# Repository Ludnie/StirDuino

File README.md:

# StirDuino
Arduino based, small form factor, low cost magnetic stir plate with PID-controlled stir speed.

## Features
- **Arduino based:** The stir plate is controlled by a Arduino nano µ-controller. A low cost and widely availible development board with extensive documentation. The firmware code is written in C++ and can be easily modified via the Arduino IDE.
- **OLED-Display:** Stir speed and set speed are highly visible displayed on a 0.9" OLED-Display.
- **Small Formfactor:** Footprint of only 70 mm x 70 mm.
- **3D-Printed Enclosure:** Enclosure is cost effectively printed. Material can be chosen depending on the use case.
- **Stir Speed:** min.: 50 rpm, max.: 1400 rpm
- **Neodynium Magnets:** Uses powerful rare earth magnets for maximum stir bar retention.
- **Remote Controlled:** Stir parameters can be remotely set via the serial interface of the µ-controller.
- **Serial Communication:** Stir parameters can be requested and logged via the serial port of the µ-controller.

## BOM
| Part               | Quantity  |
|--------------------|-----------|
| Arduino nano every |     1     |

## Upgrades and Fixes for next Version
- [ ] Implement **operating hours counter**. Operating time stored in eeprom.
- [ ] Add funktionality to **send commands** to stir plate via the serial interface. These commands may include:
    - [ ] Change mode from user input to serial input.
    - [ ] Set stir speed.
    - [ ] Set stir direction.
    - [ ] Request current stir speed.
    - [ ] Request current stir direction.
    - [ ] Request current moter power (PWM duty cycle)
    - [ ] Request current configuration Parameters (Firmware Version, operating hours, PID-Params, etc.)
- [ ] Replace potentiometer with **rotary encoder/switch**. PCB is allready designed with neccessary traces and footprint for a connector. This will enable easier input for set point and implementation of a basic menu.
- [ ] Improve fastening method for **OLED-display**.
- [ ] Put **knob** into a recessed position.
- [ ] **Liquid proof** the device (especially display).
- [ ] Implement some mechanism for **detecting a "slipping" stir bar**.

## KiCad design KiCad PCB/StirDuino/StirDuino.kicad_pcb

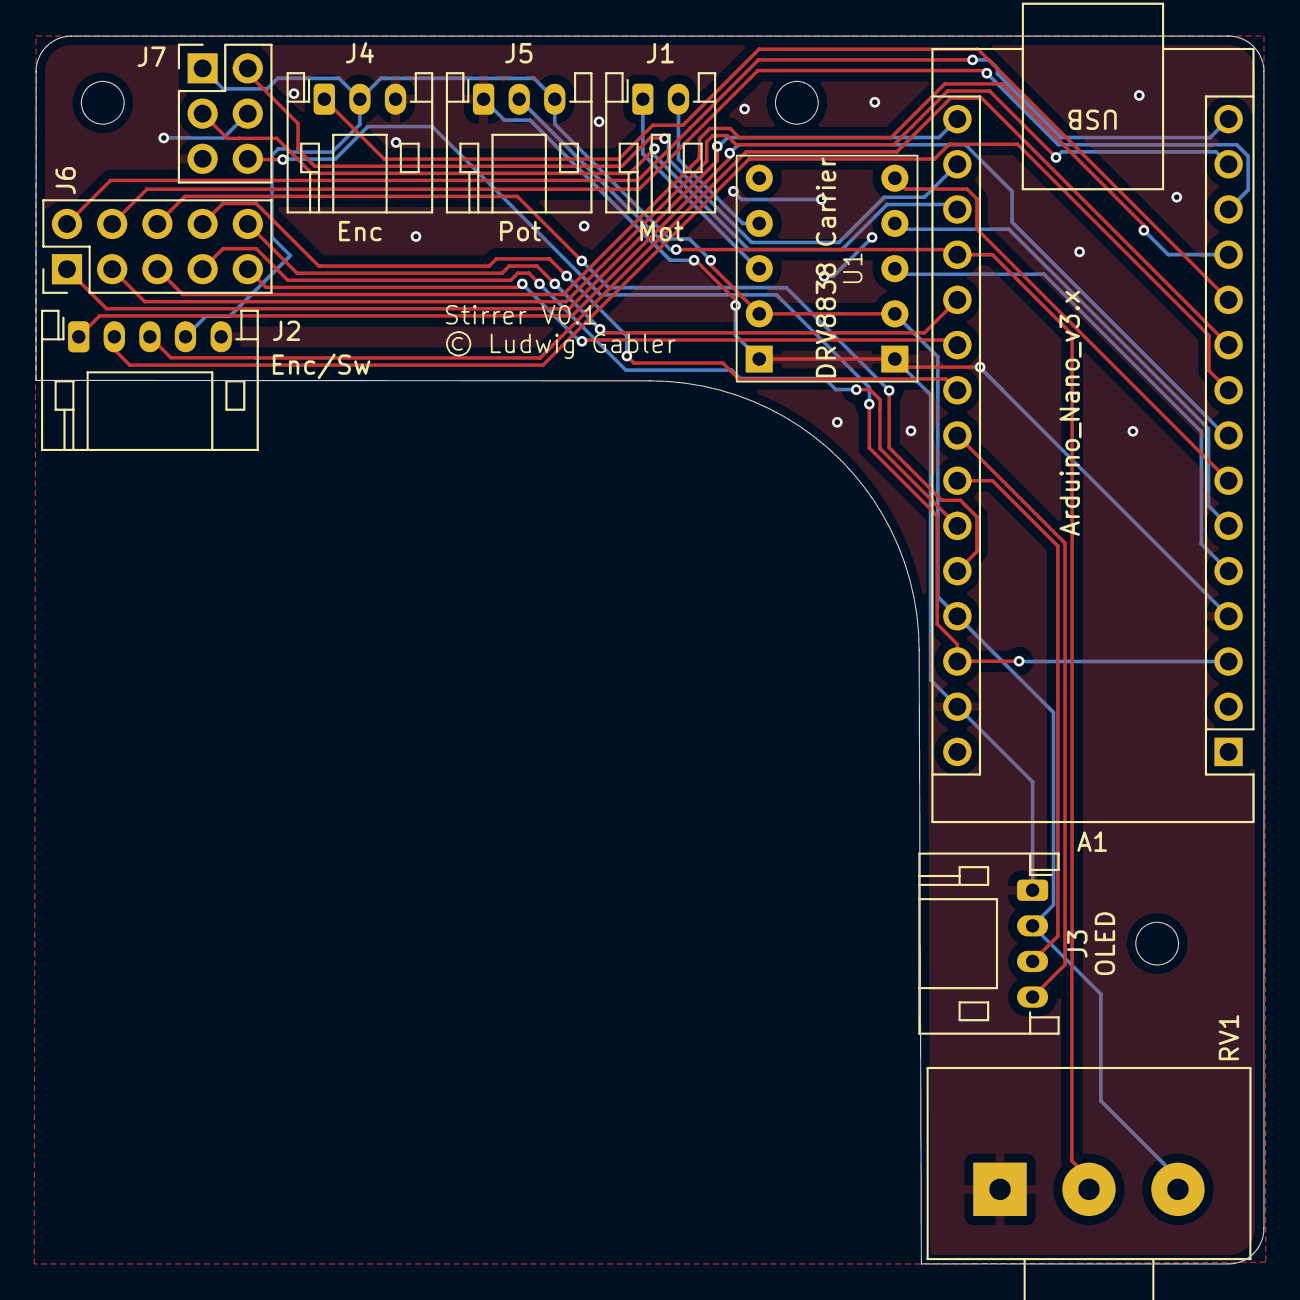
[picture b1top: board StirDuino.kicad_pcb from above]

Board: 2 copper layers, 69.0 x 69.0 mm, 10 parts (0 on the bottom side), 27 nets.

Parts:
A1: Arduino_Nano_v3.x; Arduino_Nano
J1: Mot; JST_PH_S2B-PH-K_1x02_P2.00mm_Horizontal
J2: Enc/Sw; JST_PH_S5B-PH-K_1x05_P2.00mm_Horizontal
J3: OLED; JST_PH_S4B-PH-K_1x04_P2.00mm_Horizontal
J4: Enc; JST_PH_S3B-PH-K_1x03_P2.00mm_Horizontal
J5: Pot; JST_PH_S3B-PH-K_1x03_P2.00mm_Horizontal
J6: GPIO; PinHeader_2x05_P2.54mm_Vertical
J7: Pwr; PinHeader_2x03_P2.54mm_Vertical
RV1: R_Potentiometer; Potentiometer_Alps_RK163_Single_Horizontal
U1: DRV8838 Carrier

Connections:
+5V: A1.27 (+5V), J2.4, J3.2, J4.2, J5.3, J7.1, RV1.3, U1.2 (VCC), U1.7 (VIN)
GND: A1.4 (GND), A1.29 (GND), J2.5, J3.1, J4.3, J5.1, J7.4, J7.5, RV1.1, U1.1 (GND), U1.6 (GND)
unnamed: A1.17 (3V3), J7.2
unnamed: A1.19 (A0), J5.2, RV1.2
unnamed: A1.20 (A1), J6.10
unnamed: A1.21 (A2), J6.9
unnamed: A1.22 (A3), J6.8
unnamed: A1.23 (A4), J3.4
unnamed: A1.24 (A5), J3.3
unnamed: A1.25 (A6), J6.7
unnamed: A1.26 (A7), J6.6
unnamed: A1.18 (AREF), J7.3
unnamed: A1.5 (D2), U1.3 (EN)
unnamed: A1.6 (D3), U1.4 (PH)
unnamed: A1.7 (D4), U1.5 (SLEEP)
unnamed: A1.8 (D5), J2.1
unnamed: A1.9 (D6), J2.2
unnamed: A1.10 (D7), J2.3
unnamed: A1.11 (D8), J4.1
unnamed: A1.12 (D9), J6.5
unnamed: A1.13 (D10), J6.4
unnamed: A1.14 (D11), J6.3
unnamed: A1.15 (D12), J6.2
unnamed: A1.16 (D13), J6.1
unnamed: J1.1, U1.8 (O2)
unnamed: J1.2, U1.9 (O1)
unnamed: A1.3 (~RESET), A1.28 (~RESET), J7.6

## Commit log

2024-10-29 Update README.md
    Spelling error
2024-10-29 add licenses
2024-10-29 add schematic
2024-10-29 Firmware
2024-10-30 optimized pid values
2024-10-30 improve refresh rates
2024-10-30 stabilized display readings
2024-10-30 set 0 point
2024-10-30 prettier display
2024-10-30 faster reacting display
2024-10-30 +4 to reach max rpm
2024-10-30 higher sample rate
2024-11-01 import KiCad-Files
2024-11-01 add information to schematic
2024-11-01 add information to pcb layout
2024-11-01 export PCB Layouts
2024-11-01 pcb backup
2024-11-01 add .lck to gitignore
2024-11-01 update gitignore
2024-11-01 export schematic
2024-11-08 Change pins as easy fix to get pwm on EN
2024-11-08 set PWM frequency to 64.5 kHz, so it is not audible
2024-11-14 use bigger magnets
2024-11-14 move
2024-11-28 tidy up and add comments
2024-11-28 add RotaryEncoder lib
2024-11-28 update pos in atomic block
2024-11-28 typo
2024-11-28 simplyfied program structure
2024-11-28 add comment
2025-02-11 fixed timing
2025-02-11 remove unneccessary
2025-02-15 different count for different light barrier
2025-02-15 models for SLA Printing
2025-02-15 branch for fixing bugs
2025-02-15 fixed runaway
2025-02-16 better fix and tuning
2025-02-16 better tune
2025-02-16 pid library and better tune
2025-02-16 disable debug mode
2025-02-16 clean up code
2025-02-16 clean up code and add splash screen

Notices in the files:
KiCad PCB/StirDuino/StirDuino.kicad_pcb:
© Ludwig Gabler
